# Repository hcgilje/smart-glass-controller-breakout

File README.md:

# smart-glass-controller-breakout

Breakout for controlling smart glass or electroluminescent wire. 

Based on https://github.com/sparkfun/EL_Sequencer/tree/V_2.3

To order from JLCPCB: Upload gerbers, BOM and CPL file located in the production folder.

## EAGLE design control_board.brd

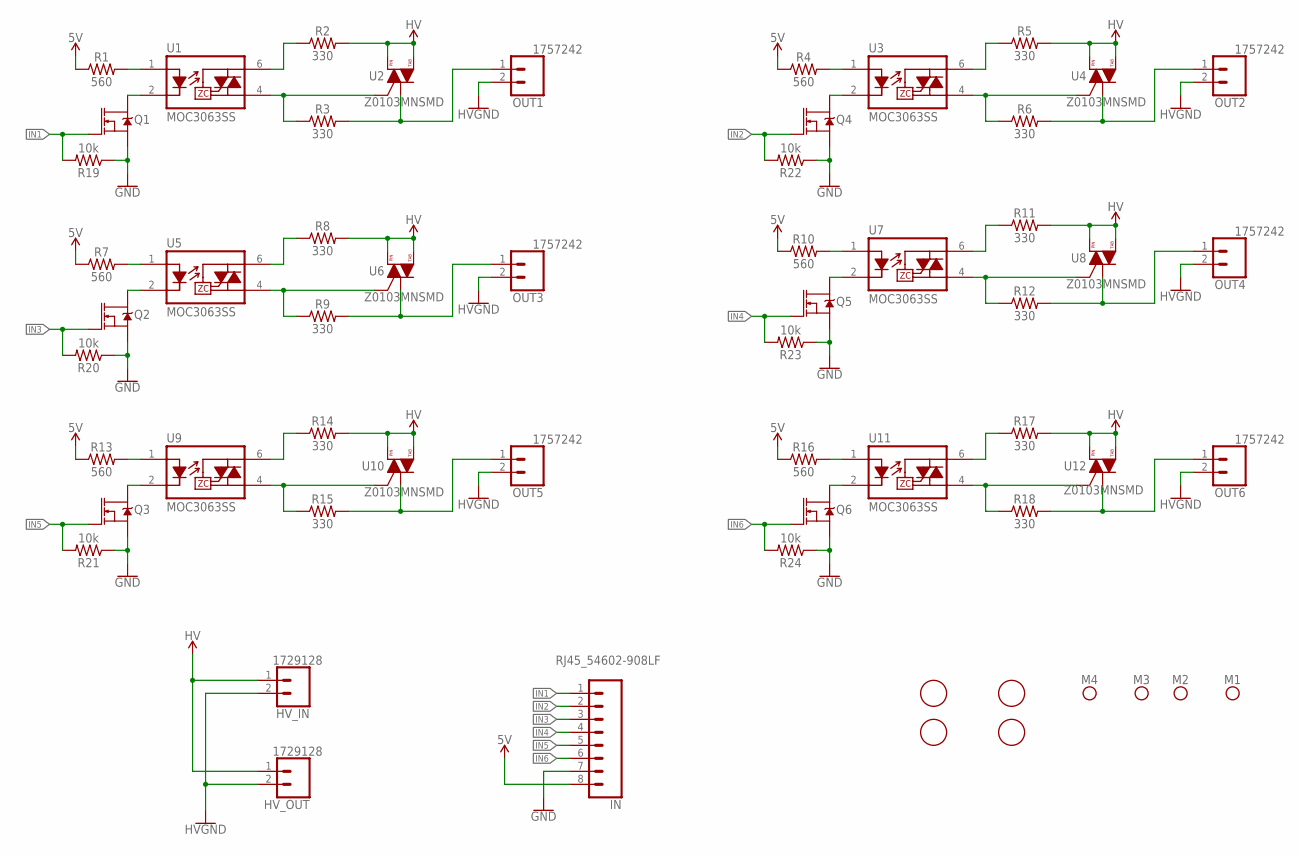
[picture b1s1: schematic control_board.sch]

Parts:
HV_IN: 1729128
HV_OUT: 1729128
IN: RJ45_54602-908LF; 54602-908LF; JLC_PART_NUMBER C2847314
M1, M2, M3, M4: NO_BOM; HOLE_ISOLATED_M2.5
OUT1, OUT2, OUT3, OUT4, OUT5, OUT6: 1757242; PHOENIX_1757242
Q1, Q2, Q3, Q4, Q5, Q6: AO3400A; SOT95P280X125-3N
R1, R4, R7, R10, R13, R16: 560; R0603; JLC_PART_NUMBER C23204
R2, R3, R5, R6, R8, R9, R11, R12, R14, R15, R17, R18: 330; R0603; JLC_PART_NUMBER C23138
R19, R20, R21, R22, R23, R24: 10k; R0603; JLC_PART_NUMBER C25804
T1, T2, T3, T4: NO_BOM; JLC_TOOLING_HOLE
U1, U3, U5, U7, U9, U11: MOC3063SS; DIP8SMD; JLC_PART_NUMBER C77950
U2, U4, U6, U8, U10, U12: Z0103MNSMD; SOT223; JLC_PART_NUMBER C163595

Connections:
5V: IN.8, R1.1, R4.1, R7.1, R10.1, R13.1, R16.1
GND: IN.7, Q1.2 (S), Q2.2 (S), Q3.2 (S), Q4.2 (S), Q5.2 (S), Q6.2 (S), R19.1, R20.1, R21.1, R22.1, R23.1, R24.1
HV: HV_IN.1, HV_OUT.1, R2.2, R5.2, R8.2, R11.2, R14.2, R17.2, U2.2 (T2), U2.4 (T2), U4.2 (T2), U4.4 (T2), U6.2 (T2), U6.4 (T2), U8.2 (T2), U8.4 (T2), U10.2 (T2), U10.4 (T2), U12.2 (T2), U12.4 (T2)
HVGND: HV_IN.2, HV_OUT.2, OUT1.2, OUT2.2, OUT3.2, OUT4.2, OUT5.2, OUT6.2
IN1: IN.1, Q1.1 (G), R19.2
IN2: IN.2, Q4.1 (G), R22.2
IN3: IN.3, Q2.1 (G), R20.2
IN4: IN.4, Q5.1 (G), R23.2
IN5: IN.5, Q3.1 (G), R21.2
IN6: IN.6, Q6.1 (G), R24.2
unnamed: R16.2, U11.1 (A)
unnamed: R1.2, U1.1 (A)
unnamed: R2.1, U1.6 (T1)
unnamed: R5.1, U3.6 (T1)
unnamed: R3.1, U1.4 (T2), U2.3 (G)
unnamed: OUT1.1, R3.2, U2.1 (T1)
unnamed: R6.1, U3.4 (T2), U4.3 (G)
unnamed: OUT2.1, R6.2, U4.1 (T1)
unnamed: Q6.3 (D), U11.2 (K)
unnamed: R8.1, U5.6 (T1)
unnamed: R9.1, U5.4 (T2), U6.3 (G)
unnamed: OUT3.1, R9.2, U6.1 (T1)
unnamed: Q5.3 (D), U7.2 (K)
unnamed: R11.1, U7.6 (T1)
unnamed: R12.1, U7.4 (T2), U8.3 (G)
unnamed: OUT4.1, R12.2, U8.1 (T1)
unnamed: R10.2, U7.1 (A)
unnamed: R14.1, U9.6 (T1)
unnamed: R15.1, U9.4 (T2), U10.3 (G)
unnamed: OUT5.1, R15.2, U10.1 (T1)
unnamed: Q4.3 (D), U3.2 (K)
unnamed: R17.1, U11.6 (T1)
unnamed: R18.1, U11.4 (T2), U12.3 (G)
unnamed: OUT6.1, R18.2, U12.1 (T1)
unnamed: Q1.3 (D), U1.2 (K)
unnamed: Q3.3 (D), U9.2 (K)
unnamed: R13.2, U9.1 (A)
unnamed: Q2.3 (D), U5.2 (K)
unnamed: R7.2, U5.1 (A)
unnamed: R4.2, U3.1 (A)

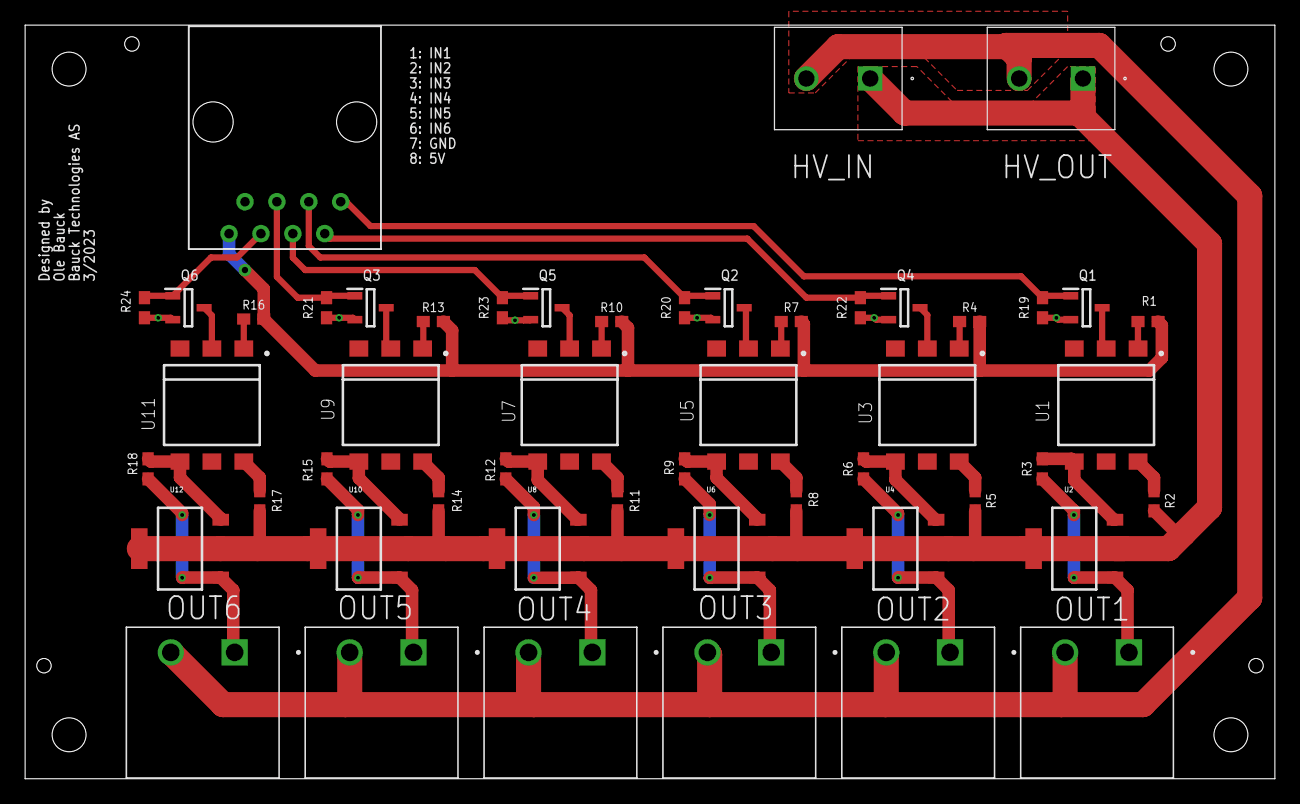
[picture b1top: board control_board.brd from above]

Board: 2 copper layers, 99.5 x 60.0 mm, 59 parts (0 on the bottom side), 40 nets.

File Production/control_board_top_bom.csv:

Comment,Designator,Footprint,LCSC Part #
10k,R19 R20 R21 R22 R23 R24,R0603,C25804
330,R2 R3 R5 R6 R8 R9 R11 R12 R14 R15 R17 R18,R0603,C23138
560,R1 R4 R7 R10 R13 R16,R0603,C23204
1729128,HV_IN HV_OUT,1729128,1729128
1757242,OUT1 OUT2 OUT3 OUT4 OUT5 OUT6,PHOENIX_1757242,C90074
AO3400A,Q1 Q2 Q3 Q4 Q5 Q6,SOT95P280X125-3N,C20917
MOC3063SS,U1 U3 U5 U7 U9 U11,DIP8SMD,C77950
RJ45_54602-908LF,IN,54602-908LF,C2847314
Z0103MNSMD,U2 U4 U6 U8 U10 U12,SOT223,C163595

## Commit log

2023-05-11 Boards produced and tested.

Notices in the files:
parts and their libraries:
SparkFun-Aesthetics: Licensing: Creative Commons ShareAlike 4.0 International - https://creativecommons.org/licenses/by-sa/4.0
